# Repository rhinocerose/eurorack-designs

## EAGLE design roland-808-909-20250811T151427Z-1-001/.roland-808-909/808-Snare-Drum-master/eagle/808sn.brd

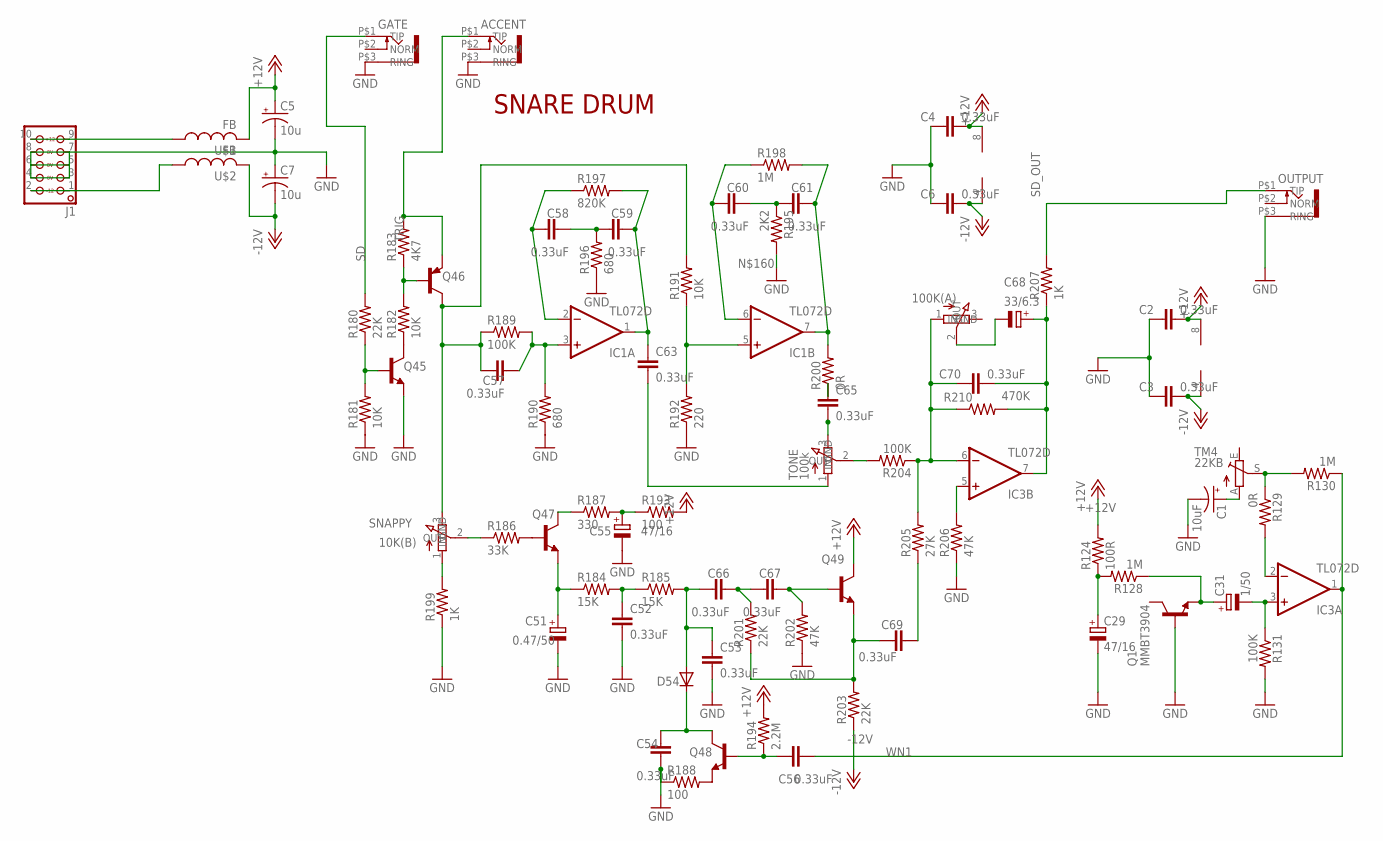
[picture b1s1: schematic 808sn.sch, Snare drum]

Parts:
ACCENT: VERTICALJACKS; KOBICONN_PJM301DM_JACK
C1: 10uF; B45181A
C2, C3, C4, C6, C52, C53, C54, C56, C57, C58, C59, C60, C61, C63, C65, C66, C67, C69, C70: 0.33uF; 0805-CAP
C5, C7: 10u; B45181A
C29: 47/16; E2,5-5
C31: 1/50; E3,5-8
C51: 0.47/50; E3,5-8
C55: 47/16; E2-5
C68: 33/6.3; E2-5
D54: 1N4148SOD-323; SOD323W_INFINEON
GATE: VERTICALJACKS; KOBICONN_PJM301DM_JACK
IC1, IC3: TL072D; SO08
J1: EUROPWR_2X05-OPEN; 2X05_EUROPWR_OPEN
LEVEL: 100K(A); ALPHA_9MM_VERTICAL
OUTPUT: VERTICALJACKS; KOBICONN_PJM301DM_JACK
Q1, Q45, Q47, Q48, Q49: MMBT3904; SOT23-BEC
Q46: MMBT3906; SOT23-BEC
R124: 100R; 0805_RESISTOR
R128, R130, R198: 1M; 0805_RESISTOR
R129, R200: 0R; 0805_RESISTOR
R131, R189, R204: 100K; 0805_RESISTOR
R180, R201, R203: 22K; 0805_RESISTOR
R181, R182, R191: 10K; 0805_RESISTOR
R183: 4K7; 0805_RESISTOR
R184, R185: 15K; 0805_RESISTOR
R186: 33K; 0805_RESISTOR
R187: 330; 0805_RESISTOR
R188, R193: 100; 0805_RESISTOR
R190, R196: 680; 0805_RESISTOR
R192: 220; 0805_RESISTOR
R194: 2.2M; 0805_RESISTOR
R195: 2K2; 0805_RESISTOR
R197: 820K; 0805_RESISTOR
R199, R207: 1K; 0805_RESISTOR
R202, R206: 47K; 0805_RESISTOR
R205: 27K; 0805_RESISTOR
R210: 470K; 0805_RESISTOR
SNAPPY: 10K(B); ALPHA_9MM_VERTICAL
TM4: 22KB; B64Y
TONE: 100k; ALPHA_9MM_VERTICAL
U$1, U$2: FB

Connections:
+12V: C2.2, C4.2, C5.+, IC1.8 (V+), IC3.8 (V+), Q49.C, R124.2, R193.2, R194.2, U$1.P$2 (2)
-12V: C3.2, C6.2, C7.-, IC1.4 (V-), IC3.4 (V-), R203.1, U$2.P$2 (2)
GND: ACCENT.P$3 (RING), C1.-, C2.1, C3.1, C4.1, C5.-, C6.1, C7.+, C29.-, C51.-, C52.2, C53.2, C54.2, C55.-, GATE.P$3 (RING), J1.3, J1.4, J1.5, J1.6, J1.7, J1.8, OUTPUT.P$3 (RING), Q1.B, Q45.E, R131.2, R181.1, R188.1, R190.1, R192.1, R195.2, R196.1, R199.1, R202.1, R206.1
unnamed: IC3.5 (+IN), R206.2
unnamed: C1.+, TM4.A
unnamed: IC3.2 (-IN), R129.2
unnamed: Q45.B, R180.1, R181.2
unnamed: Q46.B, R182.2, R183.1
unnamed: Q45.C, R182.1
unnamed: C57.2, IC1.3 (+IN), R189.2, R190.2
unnamed: C57.1, Q46.C, R189.1, R191.2, SNAPPY.3 (IN)
unnamed: J1.9, J1.10, U$1.P$1 (1)
unnamed: C58.1, IC1.2 (-IN), R197.1
unnamed: C59.2, C63.1, IC1.1 (OUT), R197.2
unnamed: C58.2, C59.1, R196.2
unnamed: C61.2, IC1.7 (OUT), R198.2, R200.2
unnamed: C60.2, C61.1, R195.1
unnamed: IC1.5 (+IN), R191.1, R192.2
unnamed: C63.2, TONE.1 (GND)
unnamed: C65.2, TONE.3 (IN)
unnamed: C65.1, R200.1
unnamed: R199.2, SNAPPY.1 (GND)
unnamed: C52.1, R184.2, R185.1
unnamed: R186.1, SNAPPY.2 (OUT)
unnamed: Q47.B, R186.2
unnamed: Q47.C, R187.1
unnamed: C55.+, R187.2, R193.1
unnamed: C51.+, Q47.E, R184.1
unnamed: C53.1, C66.1, D54.A, R185.2
unnamed: C66.2, C67.1, R201.2
unnamed: C67.2, Q49.B, R202.2
unnamed: C69.1, Q49.E, R201.1, R203.2
unnamed: Q48.E, R188.2
unnamed: C54.1, D54.C, Q48.C
unnamed: C56.1, Q48.B, R194.1
unnamed: R204.2, TONE.2 (OUT)
unnamed: C70.1, IC3.6 (-IN), LEVEL.1 (GND), R204.1, R205.2, R210.1
unnamed: C69.2, R205.1
unnamed: J1.1, J1.2, U$2.P$1 (1)
unnamed: C68.+, C70.2, IC3.7 (OUT), R207.1, R210.2
unnamed: C68.-, LEVEL.2 (OUT)
unnamed: C60.1, IC1.6 (-IN), R198.1
unnamed: C31.-, IC3.3 (+IN), R131.1
unnamed: R129.1, R130.2, TM4.S
unnamed: C31.+, Q1.E, R128.1
unnamed: C29.+, R124.1, R128.2
SD: GATE.P$1 (TIP), R180.2
SD_OUT: OUTPUT.P$1 (TIP), R207.2
TRIG: ACCENT.P$1 (TIP), Q46.E, R183.2
WN1: C56.2, IC3.1 (OUT), R130.1

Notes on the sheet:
SNARE DRUM

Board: 2 copper layers, 80 parts (5 on the bottom side), 50 nets, no tracks yet.

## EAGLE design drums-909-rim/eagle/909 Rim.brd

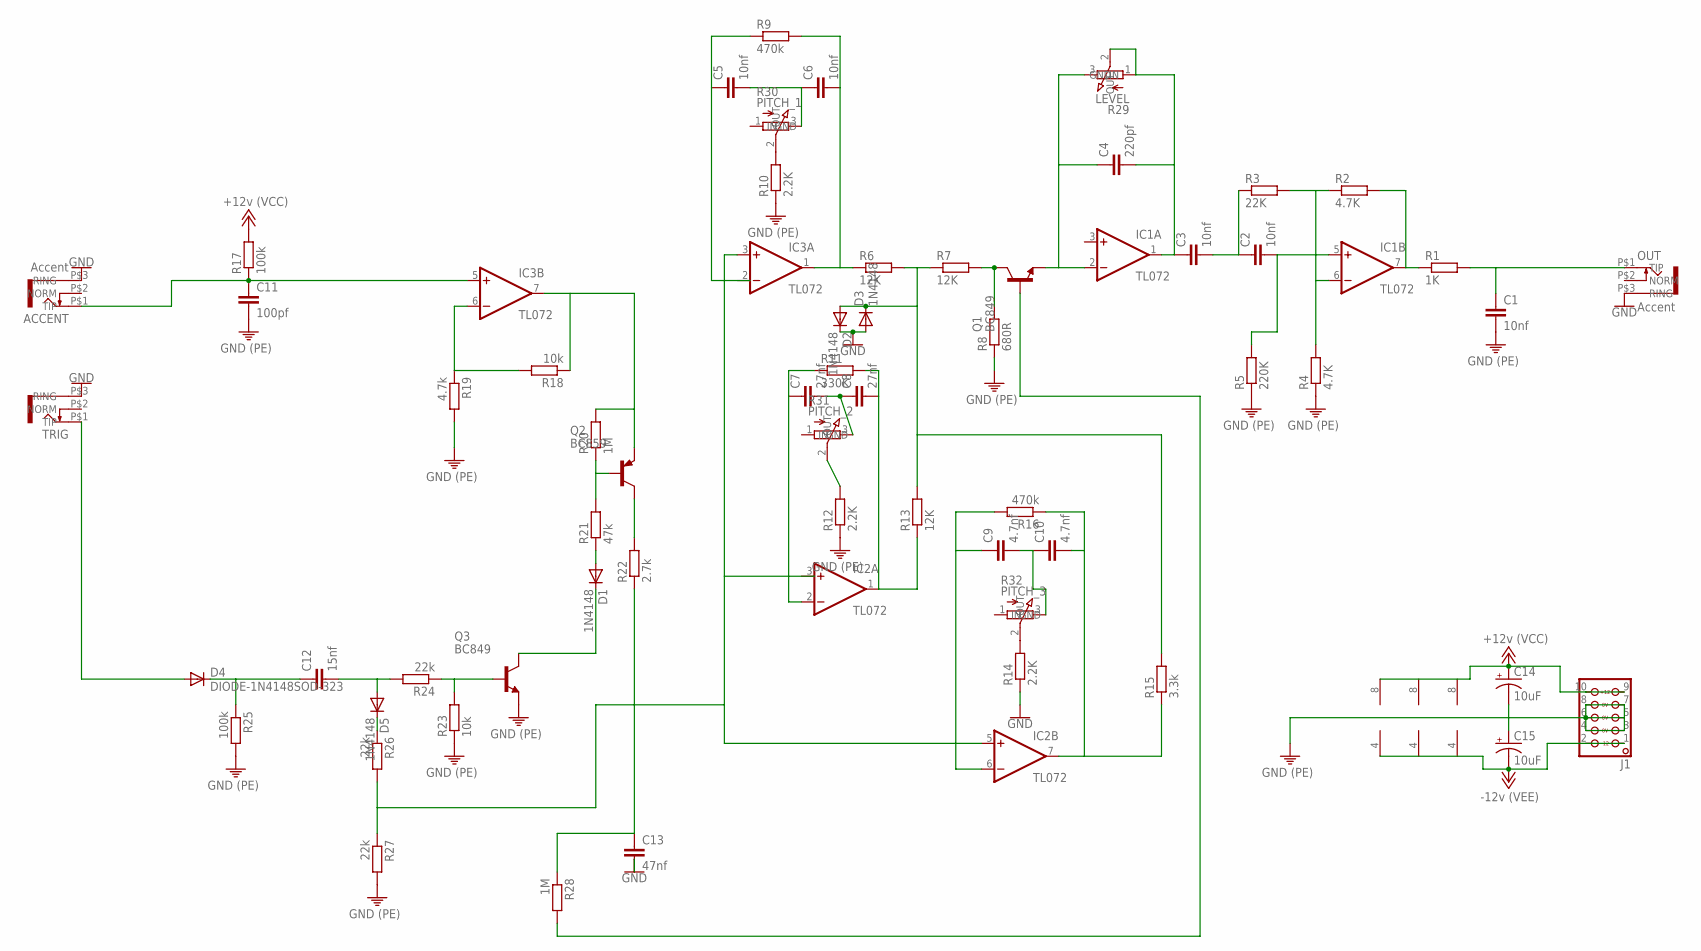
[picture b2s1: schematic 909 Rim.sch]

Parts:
ACCENT: Accent; KOBICONN_PJM301DM_JACK
C1, C2, C3, C5, C6: 10nf; C0603
C4: 220pf; C0603
C7, C8: 27nf; C0603
C9, C10: 4.7nf; C0603
C11: 100pf; C0603
C12: 15nf; C0603
C13: 47nf; C0603
C14, C15: 10uF; E2,5-5
D1, D2, D3, D5: 1N4148; SOD323W_INFINEON
D4: DIODE-1N4148SOD-323; SOD323W_INFINEON
IC1, IC2, IC3: TL072; SO08
J1: HEADER-EUROPWR_2X05-OPEN; 2X05_EUROPWR_OPEN
OUT: Accent; KOBICONN_PJM301DM_JACK
Q1, Q3: BC849; SOT23-BEC
Q2: BC859; SOT23-BEC
R1: 1K; R0603
R2, R4: 4.7K; R0603
R3: 22K; R0603
R5: 220K; R0603
R6, R7, R13: 12K; R0603
R8: 680R; R0603
R9, R16: 470k; R0603
R10, R12, R14: 2.2K; R0603
R11: 330K; R0603
R15: 3.3k; R0603
R17, R25: 100k; R0603
R18, R23: 10k; R0603
R19: 4.7k; R0603
R20, R28: 1M; R0603
R21: 47k; R0603
R22: 2.7k; R0603
R24, R26, R27: 22k; R0603
R29: LEVEL; 9MM_PLS
R30: PITCH_1; 9MM_PLS
R31: PITCH_2; 9MM_PLS
R32: PITCH_3; 9MM_PLS
TRIG: JACK_KOBICONN_PJM301DM_V2; KOBICONN_PJM301DM_JACK

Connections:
+12V: C14.+, IC1.8 (V+), J1.9, J1.10, R17.2
-12V: C15.-, IC1.4 (V-), J1.1, J1.2
GND: ACCENT.P$3 (RING), C1.2, C11.2, C13.2, C14.-, C15.+, D2.C, D3.A, J1.3, J1.4, J1.5, J1.6, J1.7, J1.8, OUT.P$3 (RING), Q3.E, R4.1, R5.1, R8.1, R10.1, R12.1, R14.1, R19.2, R23.1, R25.2, R27.2, TRIG.P$3 (RING)
unnamed: IC1.7 (OUT), R1.1, R2.2
unnamed: C3.1, C4.2, IC1.1 (OUT), R29.1 (GND), R29.2 (OUT)
unnamed: C2.1, C3.2, R3.1
unnamed: C2.2, IC1.5 (+IN), R5.2
unnamed: IC1.6 (-IN), R2.1, R3.2, R4.2
unnamed: C1.1, OUT.P$1 (TIP), R1.2
unnamed: C4.1, IC1.2 (-IN), Q1.E, R29.3 (IN)
unnamed: D2.A, D3.C, R6.2, R7.1, R13.2, R15.2
unnamed: C6.2, IC3.1 (OUT), R6.1, R9.2
unnamed: Q1.C, R7.2, R8.2
unnamed: C5.1, R9.1
unnamed: R10.2, R30.2 (OUT)
unnamed: C7.2, C8.1, R31.3 (IN)
unnamed: C9.2, C10.1, R32.3 (IN)
unnamed: C10.2, IC2.7 (OUT), R15.1, R16.1
unnamed: C5.2, C6.1, R30.3 (IN)
unnamed: C8.2, IC2.1 (OUT), R11.2, R13.1
unnamed: C9.1, IC2.6 (-IN), R16.2
unnamed: Q1.B, R28.2
unnamed: ACCENT.P$1 (TIP), C11.1, IC3.5 (+IN), R17.1
unnamed: IC3.6 (-IN), R18.2, R19.1
unnamed: IC3.7 (OUT), Q2.E, R18.1, R20.2
unnamed: Q2.B, R20.1, R21.2
unnamed: Q2.C, R22.2
unnamed: D1.A, R21.1
unnamed: D5.C, R26.1
unnamed: C12.1, D4.C, R25.1
unnamed: C12.2, D5.A, R24.2
unnamed: IC2.5 (+IN), IC3.3 (+IN), R26.2, R27.1
unnamed: Q3.B, R23.2, R24.1
unnamed: D1.C, Q3.C
unnamed: C13.1, R22.1, R28.1
unnamed: R12.2, R31.2 (OUT)
unnamed: D4.A, TRIG.P$1 (TIP)
unnamed: R14.2, R32.2 (OUT)
unnamed: C7.1, IC2.2 (-IN), R11.1
V+: IC2.8 (V+), IC3.8 (V+)
V-: IC2.4 (V-), IC3.4 (V-)

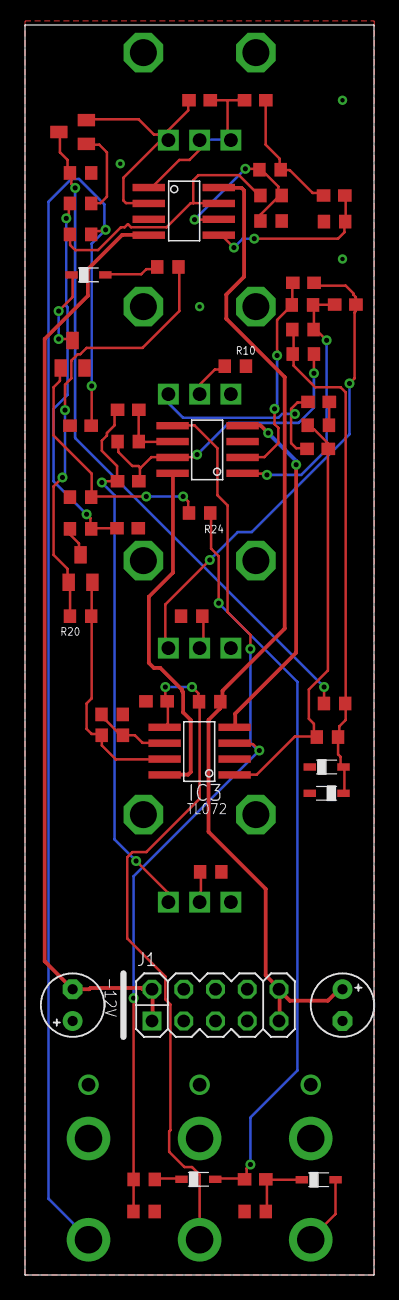
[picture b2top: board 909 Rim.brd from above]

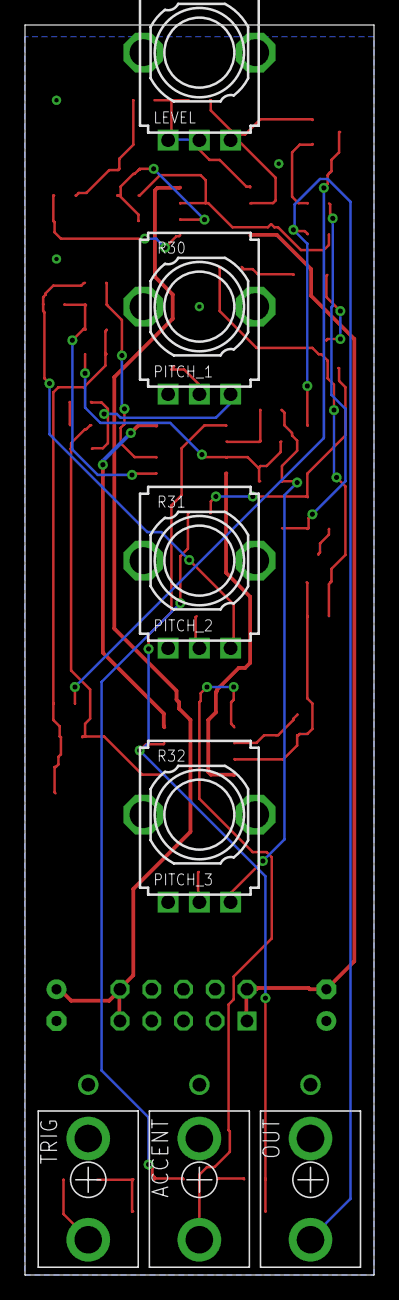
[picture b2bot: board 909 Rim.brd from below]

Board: 2 copper layers, 27.9 x 100.0 mm, 62 parts (7 on the bottom side), 41 nets.

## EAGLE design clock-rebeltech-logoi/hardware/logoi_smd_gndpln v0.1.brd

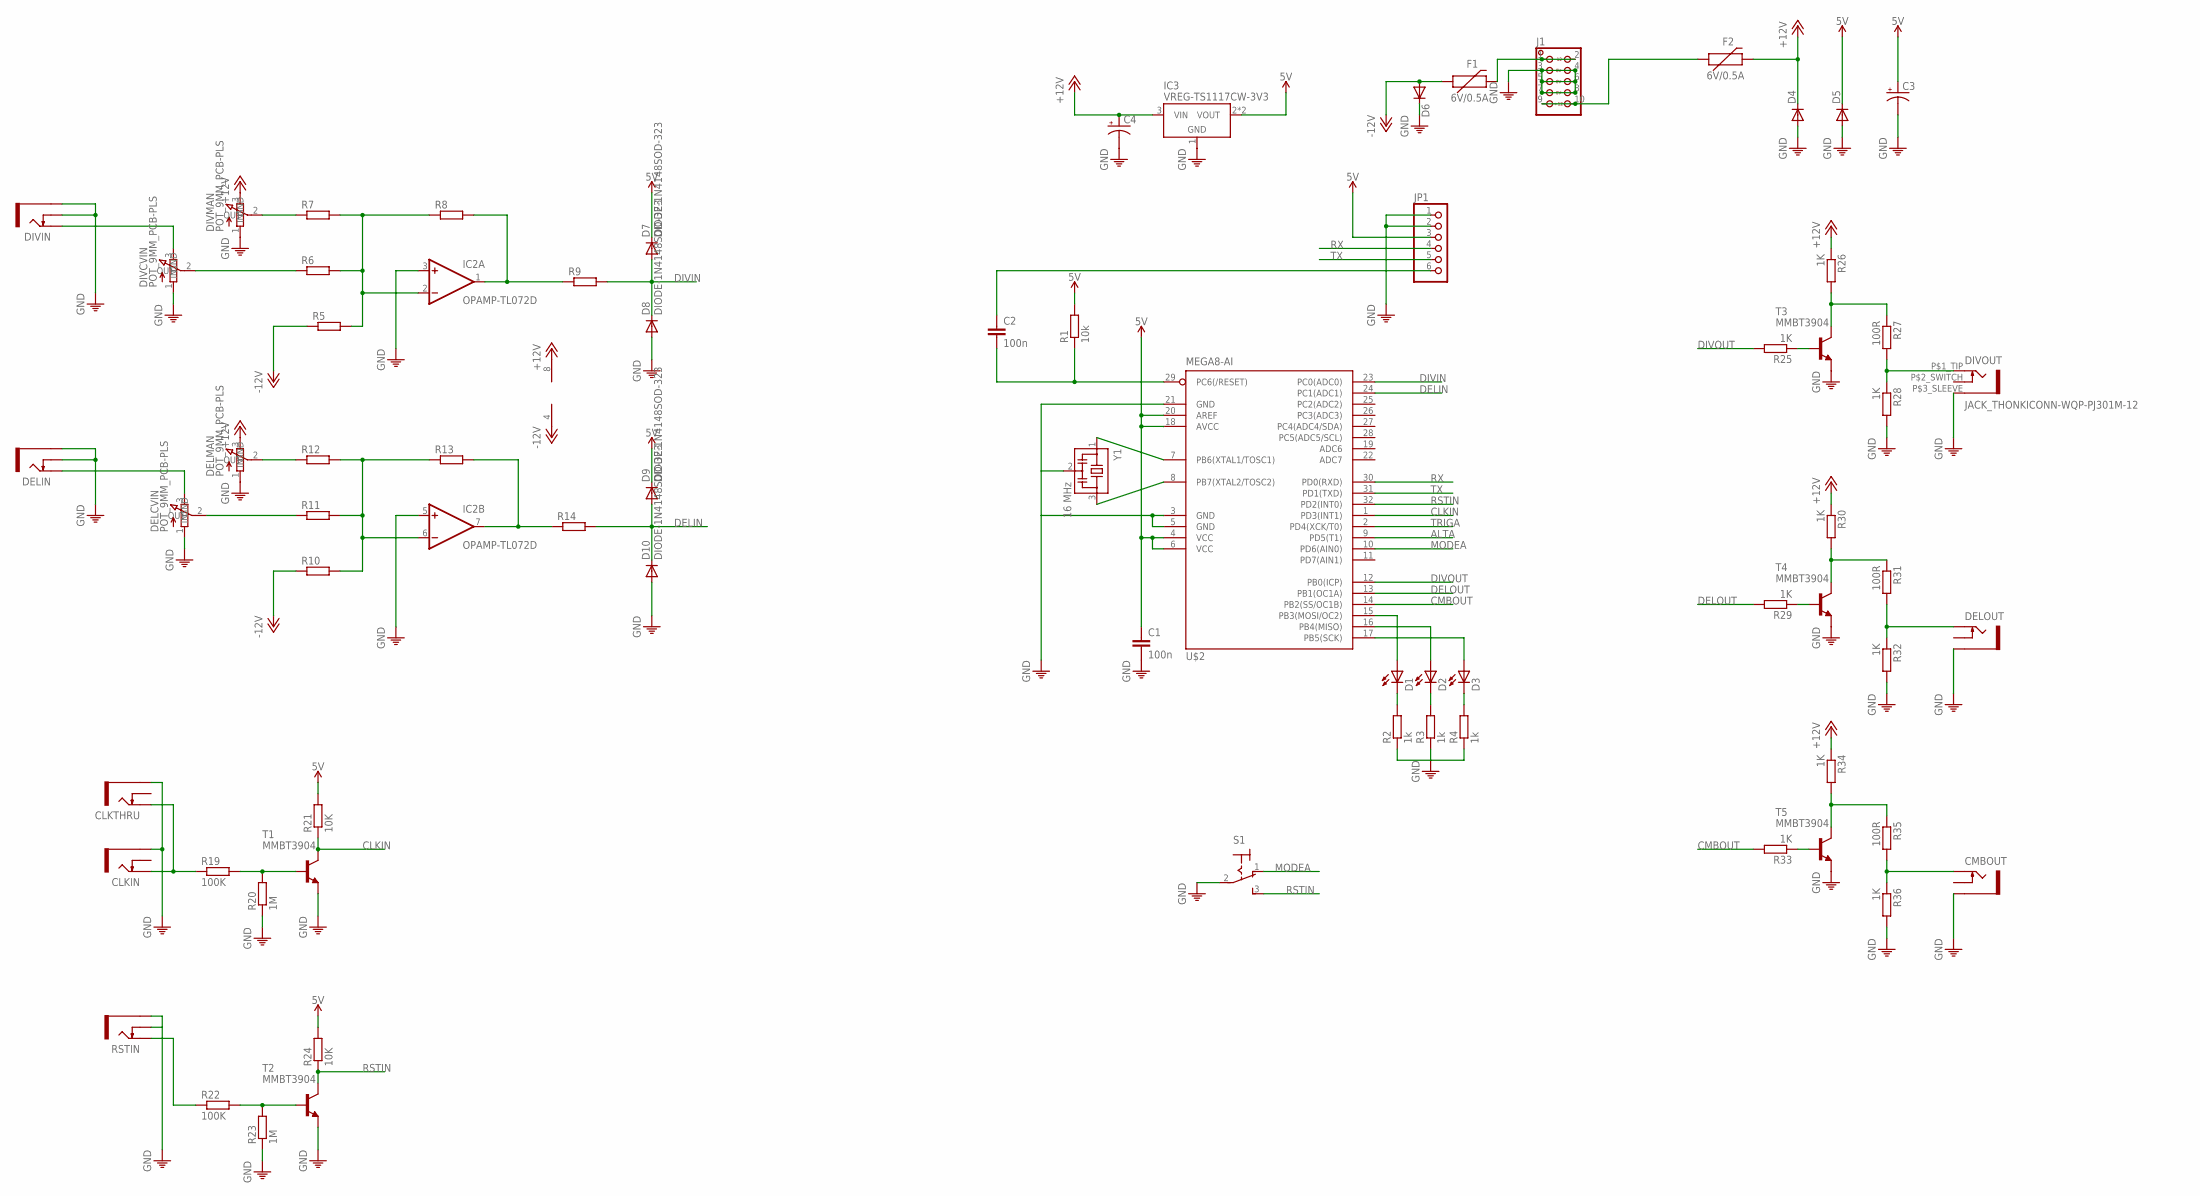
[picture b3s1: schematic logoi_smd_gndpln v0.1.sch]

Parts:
C1, C2: 100n; C0603K
C3, C4: CAPACITOR_POLARIZED-USE2.5-5; E2,5-5
CLKIN: JACK_THONKICONNNEW; WQP-PJ301M-12_JACK
CLKTHRU: JACK_THONKICONNNEW; WQP-PJ301M-12_JACK
CMBOUT: JACK_THONKICONNNEW; WQP-PJ301M-12_JACK
D1, D2, D3: LED3MM
D4, D5, D6: DIODE-DO-214AC; DO-214AC
D7, D8, D9, D10: DIODE-1N4148SOD-323; SOD323W_INFINEON
DELCVIN: POT_9MM_PCB-PLS; 9MM_PLS
DELIN: JACK_THONKICONNNEW; WQP-PJ301M-12_JACK
DELMAN: POT_9MM_PCB-PLS; 9MM_PLS
DELOUT: JACK_THONKICONNNEW; WQP-PJ301M-12_JACK
DIVCVIN: POT_9MM_PCB-PLS; 9MM_PLS
DIVIN: JACK_THONKICONNNEW; WQP-PJ301M-12_JACK
DIVMAN: POT_9MM_PCB-PLS; 9MM_PLS
DIVOUT: JACK_THONKICONN-WQP-PJ301M-12; WQP-PJ301M-12_JACK
F1, F2: 6V/0.5A; 1206
IC2: OPAMP-TL072D; SO08
IC3: VREG-TS1117CW-3V3; SOT223
J1: HEADER-EUROPWR_2X05-OPEN; 2X05_EUROPWR_OPEN
JP1: PINHD-1X6; 1X06
R1: 10k; R0603
R2, R3, R4: 1k; R0603
R5, R6, R7, R8, R9, R10, R11, R12, R13, R14: RESISTOR-EU_R0603; R0603
R19, R22: 100K; R0603
R20, R23: 1M; R0603
R21, R24: 10K; R0603
R25, R26, R28, R29, R30, R32, R33, R34, R36: 1K; R0603
R27, R31, R35: 100R; R0603
RSTIN: JACK_THONKICONNNEW; WQP-PJ301M-12_JACK
S1: SWITCH-SPDT-320-916; 320-916
T1, T2, T3, T4, T5: MMBT3904; SOT23-BEC
U$2: MEGA8-AI; TQFP32-08
Y1: 16 MHz; CSTCR6M

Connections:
5V: C1.1, C3.+, D5.C, D7.C, D9.C, IC3.2 (VOUT), IC3.4 (VOUT), JP1.3, R1.2, R21.2, R24.2, U$2.4 (VCC), U$2.6 (VCC), U$2.18 (AVCC), U$2.20 (AREF)
+12V: C4.+, D4.C, DELMAN.3 (IN), DIVMAN.3 (IN), F2.2, IC2.8 (V+), IC3.3 (VIN), R26.1, R30.1, R34.1
-12V: D6.A, F1.1, IC2.4 (V-), R5.1, R10.1
ALTA: U$2.9 (PD5(T1))
CLKIN: R21.1, T1.C, U$2.1 (PD3(INT1))
CMBOUT: R33.2, U$2.14 (PB2(SS/OC1B))
DELIN: D9.A, D10.C, R14.2, U$2.24 (PC1(ADC1))
DELOUT: R29.2, U$2.13 (PB1(OC1A))
DIVIN: D7.A, D8.C, R9.2, U$2.23 (PC0(ADC0))
DIVOUT: R25.2, U$2.12 (PB0(ICP))
MODEA: S1.1 (O), U$2.10 (PD6(AIN0))
unnamed: U$2.7 (PB6(XTAL1/TOSC1)), Y1.1
unnamed: U$2.8 (PB7(XTAL2/TOSC2)), Y1.3
unnamed: F1.2, J1.1, J1.2
unnamed: C2.2, R1.1, U$2.29 (PC6(/RESET))
unnamed: C2.1, JP1.6
unnamed: F2.1, J1.9, J1.10
unnamed: IC2.2 (-IN), R5.2, R6.2, R7.2, R8.1
unnamed: IC2.1 (OUT), R8.2, R9.1
unnamed: R25.1, T3.B
unnamed: IC2.6 (-IN), R10.2, R11.2, R12.2, R13.1
unnamed: R26.2, R27.1, T3.C
unnamed: IC2.7 (OUT), R13.2, R14.1
unnamed: DIVOUT.P$1_TIP (2), R27.2, R28.1
unnamed: DIVCVIN.3 (IN), DIVIN.P$1_TIP (TIP)
unnamed: DIVCVIN.2 (OUT), R6.1
unnamed: DIVMAN.2 (OUT), R7.1
unnamed: D1.K (C), R2.2
unnamed: D2.K (C), R3.2
unnamed: D3.K (C), R4.2
unnamed: D1.A, U$2.15 (PB3(MOSI/OC2))
unnamed: D2.A, U$2.16 (PB4(MISO))
unnamed: D3.A, U$2.17 (PB5(SCK))
unnamed: DELCVIN.2 (OUT), R11.1
unnamed: DELCVIN.3 (IN), DELIN.P$1_TIP (TIP)
unnamed: DELMAN.2 (OUT), R12.1
unnamed: CLKIN.P$1_TIP (TIP), CLKTHRU.P$1_TIP (TIP), R19.1
unnamed: R19.2, R20.2, T1.B
unnamed: R22.1, RSTIN.P$1_TIP (TIP)
unnamed: R22.2, R23.2, T2.B
unnamed: R29.1, T4.B
unnamed: R30.2, R31.1, T4.C
unnamed: DELOUT.P$1_TIP (TIP), R31.2, R32.1
unnamed: R33.1, T5.B
unnamed: R34.2, R35.1, T5.C
unnamed: CMBOUT.P$1_TIP (TIP), R35.2, R36.1
PE: C1.2, C3.-, C4.-, CLKIN.P$3_SLEEVE (SLEEVE), CLKTHRU.P$3_SLEEVE (SLEEVE), CMBOUT.P$3_SLEEVE (SLEEVE), D4.A, D5.A, D6.C, D8.A, D10.A, DELCVIN.1 (GND), DELIN.P$2_SWITCH (SWITCH), DELIN.P$3_SLEEVE (SLEEVE), DELMAN.1 (GND), DELOUT.P$3_SLEEVE (SLEEVE), DIVCVIN.1 (GND), DIVIN.P$2_SWITCH (SWITCH), DIVIN.P$3_SLEEVE (SLEEVE), DIVMAN.1 (GND), DIVOUT.P$3_SLEEVE (1), IC2.3 (+IN), IC2.5 (+IN), IC3.1 (GND), J1.3, J1.4, J1.5, J1.6, J1.7, J1.8, JP1.1, JP1.2, R2.1, R3.1, R4.1, R20.1, R23.1, R28.2, R32.2, R36.2, RSTIN.P$2_SWITCH (SWITCH), RSTIN.P$3_SLEEVE (SLEEVE), S1.2, T1.E, T2.E, T3.E, T4.E, T5.E, U$2.3 (GND), U$2.5 (GND), U$2.21 (GND), Y1.2
RSTIN: R24.1, S1.3 (S), T2.C, U$2.32 (PD2(INT0))
RX: JP1.4, U$2.30 (PD0(RXD))
TRIGA: U$2.2 (PD4(XCK/T0))
TX: JP1.5, U$2.31 (PD1(TXD))

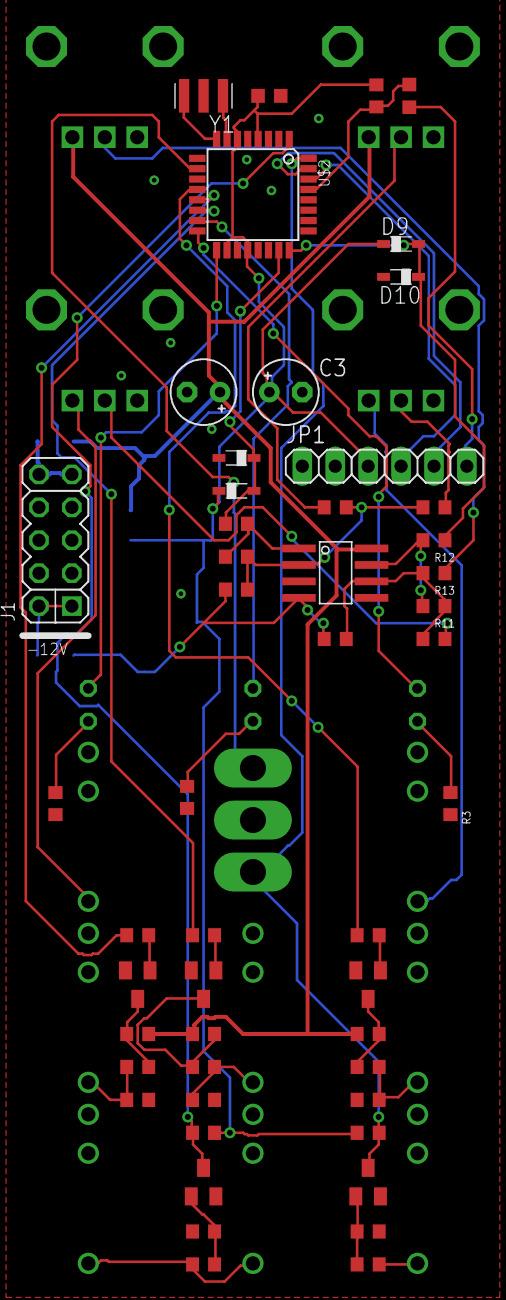
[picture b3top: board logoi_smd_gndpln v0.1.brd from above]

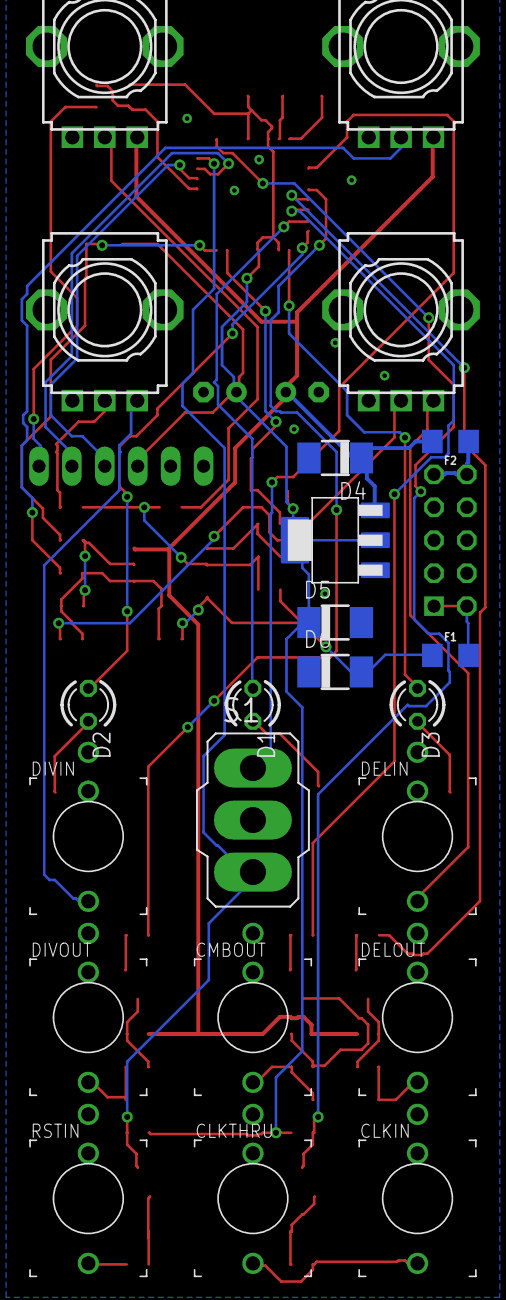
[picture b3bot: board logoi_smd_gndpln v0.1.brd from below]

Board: 2 copper layers, 72 parts (22 on the bottom side), 49 nets.

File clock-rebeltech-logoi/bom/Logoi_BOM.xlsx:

R19 | 100K | RESISTOR-EU_R0603 | R0603
R22 | 100K | RESISTOR-EU_R0603 | R0603
C1 | 100n | CAPACITOR-EUC0603K | C0603K
C2 | 100n | CAPACITOR-EUC0603K | C0603K
C6 | 100n | CAPACITOR-EUC0603K | C0603K
C7 | 100n | CAPACITOR-EUC0603K | C0603K
R27 | 100R | RESISTOR-EU_R0603 | R0603
R31 | 100R | RESISTOR-EU_R0603 | R0603
R35 | 100R | RESISTOR-EU_R0603 | R0603
R1 | 10k | RESISTOR-EU_R0603 | R0603
R21 | 10K | RESISTOR-EU_R0603 | R0603
R24 | 10K | RESISTOR-EU_R0603 | R0603
C4 | 10u | CAPACITOR_POLARIZED-USB | PANASONIC_B
C5 | 10u | CAPACITOR_POLARIZED-USB | PANASONIC_B
R5 | 120k | RESISTOR-EU_R0603 | R0603
R7 | 120k | RESISTOR-EU_R0603 | R0603
R10 | 120k | RESISTOR-EU_R0603 | R0603
R12 | 120k | RESISTOR-EU_R0603 | R0603
Y1 | 16 MHz | CSTCR6M00G53Z | CSTCR6M
R2 | 1k | RESISTOR-EU_R0603 | R0603
R3 | 1k | RESISTOR-EU_R0603 | R0603
R4 | 1k | RESISTOR-EU_R0603 | R0603
R25 | 1K | RESISTOR-EU_R0603 | R0603
R26 | 1K | RESISTOR-EU_R0603 | R0603
R28 | 1K | RESISTOR-EU_R0603 | R0603
R29 | 1K | RESISTOR-EU_R0603 | R0603
R30 | 1K | RESISTOR-EU_R0603 | R0603
R32 | 1K | RESISTOR-EU_R0603 | R0603
R33 | 1K | RESISTOR-EU_R0603 | R0603
R34 | 1K | RESISTOR-EU_R0603 | R0603
R36 | 1K | RESISTOR-EU_R0603 | R0603
R20 | 1M | RESISTOR-EU_R0603 | R0603
R23 | 1M | RESISTOR-EU_R0603 | R0603
R6 | 51k | RESISTOR-EU_R0603 | R0603
R8 | 51k | RESISTOR-EU_R0603 | R0603
R9 | 51k | RESISTOR-EU_R0603 | R0603
R11 | 51k | RESISTOR-EU_R0603 | R0603
R13 | 51k | RESISTOR-EU_R0603 | R0603
R14 | 51k | RESISTOR-EU_R0603 | R0603
F1 | 6V/0.5A | FUSE-PPTC_HALF-AMP | L1206
F2 | 6V/0.5A | FUSE-PPTC_HALF-AMP | L1206
IC1 | 7805DT | 7805DT | TO252
U$2 | ATMEGA328 | MEGA8-AI | TQFP32-08
D7 | DIODE-1N4148SOD-323 | DIODE-1N4148SOD-323 | SOD323W_INFINEON | ****DNP*****
D8 | DIODE-1N4148SOD-323 | DIODE-1N4148SOD-323 | SOD323W_INFINEON | ****DNP*****
D9 | DIODE-1N4148SOD-323 | DIODE-1N4148SOD-323 | SOD323W_INFINEON | ****DNP*****
D10 | DIODE-1N4148SOD-323 | DIODE-1N4148SOD-323 | SOD323W_INFINEON | ****DNP*****
J1 | HEADER-EUROPWR_2X05-OPE | HEADER-EUROPWR_2X05-OPEN | 2X05_EUROPWR_OPEN
CLKIN | JACK_THONKICONNNEW | JACK_THONKICONNNEW | WQP-PJ301M-12_JACK
CLKTHRU | JACK_THONKICONNNEW | JACK_THONKICONNNEW | WQP-PJ301M-12_JACK
CMBOUT | JACK_THONKICONNNEW | JACK_THONKICONNNEW | WQP-PJ301M-12_JACK
DELIN | JACK_THONKICONNNEW | JACK_THONKICONNNEW | WQP-PJ301M-12_JACK
DELOUT | JACK_THONKICONNNEW | JACK_THONKICONNNEW | WQP-PJ301M-12_JACK
DIVIN | JACK_THONKICONNNEW | JACK_THONKICONNNEW | WQP-PJ301M-12_JACK
DIVOUT | JACK_THONKICONNNEW | JACK_THONKICONNNEW | WQP-PJ301M-12_JACK
RSTIN | JACK_THONKICONNNEW | JACK_THONKICONNNEW | WQP-PJ301M-12_JACK
T1 | MMBT3904 | TRANSISTOR-NPN-MMBT3904LT1SO | T23-BEC SOT23-BEC
T2 | MMBT3904 | TRANSISTOR-NPN-MMBT3904LT1SO | T23-BEC SOT23-BEC
T3 | MMBT3904 | TRANSISTOR-NPN-MMBT3904LT1SO | T23-BEC SOT23-BEC
T4 | MMBT3904 | TRANSISTOR-NPN-MMBT3904LT1SO | T23-BEC SOT23-BEC
T5 | MMBT3904 | TRANSISTOR-NPN-MMBT3904LT1SO | T23-BEC SOT23-BEC
IC2 | OPAMP-TL072D | OPAMP-TL072D | SO08
DELCVIN | POT_9MM_PCB-PLS | POT_9MM_PCB-PLS | 9MM_PLS
DELMAN | POT_9MM_PCB-PLS | POT_9MM_PCB-PLS | 9MM_PLS
DIVCVIN | POT_9MM_PCB-PLS | POT_9MM_PCB-PLS | 9MM_PLS
DIVMAN | POT_9MM_PCB-PLS | POT_9MM_PCB-PLS | 9MM_PLS
D4 | SS12 | DIODE-DO-214AC | DO-214AC
D6 | SS12 | DIODE-DO-214AC | DO-214AC
Part | Value | Device | Package
D1 |  | LED3MM | LED3MM
D2 |  | LED3MM | LED3MM
D3 |  | LED3MM | LED3MM
JP1 |  | PINHD-1X6 | 1X06
S1 |  | SWITCH-SPDT-320-916 | 320-916

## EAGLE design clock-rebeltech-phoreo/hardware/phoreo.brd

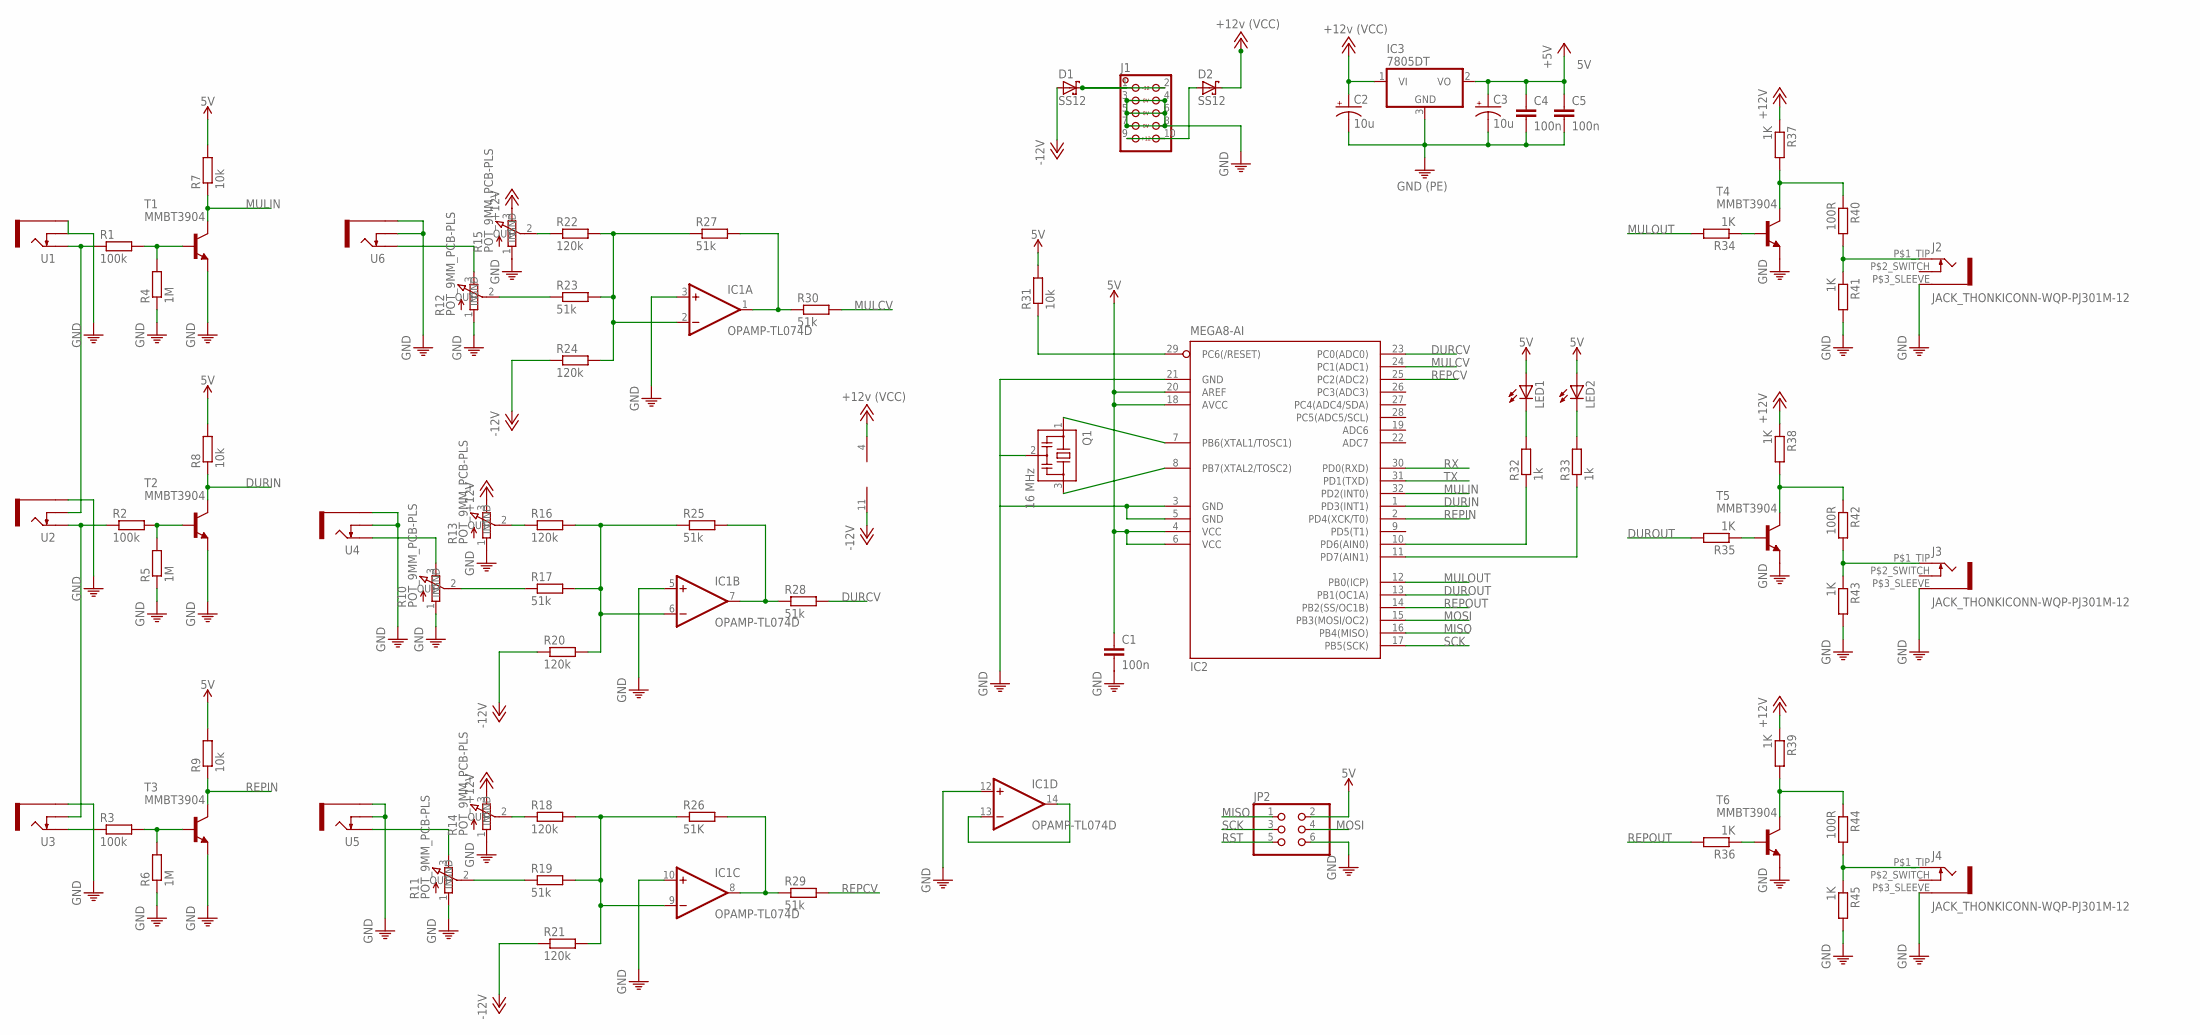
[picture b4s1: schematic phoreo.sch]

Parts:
C1: 100n; C0603K
C2, C3: 10u; PANASONIC_B
C4, C5: 100n; C0603
D1, D2: SS12; SMA_DO214AC
IC1: OPAMP-TL074D; SO14
IC2: MEGA8-AI; TQFP32-08
IC3: 7805DT; TO252
J1: HEADER-EUROPWR_2X05-OPEN; 2X05_EUROPWR_OPEN
J2, J3, J4: JACK_THONKICONN-WQP-PJ301M-12; WQP-PJ301M-12_JACK
JP2: PINHD-2X3; 2X03
LED1, LED2: LED3MM
Q1: 16 MHz; CSTCR6M
R1, R2, R3: 100k; R0603
R4, R5, R6: 1M; R0603
R7, R8, R9, R31: 10k; R0603
R10, R11, R12, R13, R14, R15: POT_9MM_PCB-PLS; 9MM_PLS
R16, R18, R20, R21, R22, R24: 120k; R0603
R17, R19, R23, R25, R27, R28, R29, R30: 51k; R0603
R26: 51K; R0603
R32, R33: 1k; R0603
R34, R35, R36, R37, R38, R39, R41, R43, R45: 1K; R0603
R40, R42, R44: 100R; R0603
T1, T2, T3, T4, T5, T6: MMBT3904; SOT23-BEC
U1, U2, U3, U4, U5, U6: mulcv; WQP-PJ301M-12_JACK

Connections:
5V: C1.1, C3.+, C4.1, C5.1, IC2.4 (VCC), IC2.6 (VCC), IC2.18 (AVCC), IC2.20 (AREF), IC3.2 (VO), JP2.2, LED1.A, LED2.A, R7.2, R8.2, R9.2, R31.2
+12V: C2.+, D2.C, IC1.4 (V+), IC3.1 (VI), R13.3 (IN), R14.3 (IN), R15.3 (IN), R37.1, R38.1, R39.1
-12V: D1.A, IC1.11 (V-), R20.1, R21.1, R24.1
DURCV: IC2.23 (PC0(ADC0)), R28.2
DURIN: IC2.1 (PD3(INT1)), R8.1, T2.C
DUROUT: IC2.13 (PB1(OC1A)), R35.2
MISO: IC2.16 (PB4(MISO)), JP2.1
MOSI: IC2.15 (PB3(MOSI/OC2)), JP2.4
MULCV: IC2.24 (PC1(ADC1)), R30.2
MULIN: IC2.32 (PD2(INT0)), R7.1, T1.C
MULOUT: IC2.12 (PB0(ICP)), R34.2
unnamed: IC2.7 (PB6(XTAL1/TOSC1)), Q1.1
unnamed: D1.C, J1.1, J1.2
unnamed: IC2.8 (PB7(XTAL2/TOSC2)), Q1.3
unnamed: IC2.29 (PC6(/RESET)), R31.1
unnamed: R34.1, T4.B
unnamed: D2.A, J1.9, J1.10
unnamed: IC2.10 (PD6(AIN0)), R32.1
unnamed: IC2.11 (PD7(AIN1)), R33.1
unnamed: LED1.K (C), R32.2
unnamed: LED2.K (C), R33.2
unnamed: IC1.2 (-IN), R22.2, R23.2, R24.2, R27.1
unnamed: IC1.1 (OUT), R27.2, R30.1
unnamed: IC1.6 (-IN), R16.2, R17.2, R20.2, R25.1
unnamed: IC1.7 (OUT), R25.2, R28.1
unnamed: R10.3 (IN), U4.P$1_TIP (TIP)
unnamed: R10.2 (OUT), R17.1
unnamed: R12.3 (IN), U6.P$1_TIP (TIP)
unnamed: R12.2 (OUT), R23.1
unnamed: R15.2 (OUT), R22.1
unnamed: R13.2 (OUT), R16.1
unnamed: IC1.9 (-IN), R18.2, R19.2, R21.2, R26.1
unnamed: IC1.8 (OUT), R26.2, R29.1
unnamed: R11.3 (IN), U5.P$1_TIP (TIP)
unnamed: R11.2 (OUT), R19.1
unnamed: R14.2 (OUT), R18.1
unnamed: IC1.13 (-IN), IC1.14 (OUT)
unnamed: R37.2, R40.1, T4.C
unnamed: J2.P$1_TIP (2), R40.2, R41.1
unnamed: R35.1, T5.B
unnamed: R38.2, R42.1, T5.C
unnamed: J3.P$1_TIP (2), R42.2, R43.1
unnamed: R36.1, T6.B
unnamed: R39.2, R44.1, T6.C
unnamed: J4.P$1_TIP (2), R44.2, R45.1
unnamed: R1.1, U1.P$1_TIP (TIP), U2.P$2_SWITCH (SWITCH)
unnamed: R1.2, R4.2, T1.B
unnamed: R2.1, U2.P$1_TIP (TIP), U3.P$2_SWITCH (SWITCH)
unnamed: R2.2, R5.2, T2.B
unnamed: R3.1, U3.P$1_TIP (TIP)
unnamed: R3.2, R6.2, T3.B
PE: C1.2, C2.-, C3.-, C4.2, C5.2, IC1.3 (+IN), IC1.5 (+IN), IC1.10 (+IN), IC1.12 (+IN), IC2.3 (GND), IC2.5 (GND), IC2.21 (GND), IC3.3 (GND), J1.3, J1.4, J1.5, J1.6, J1.7, J1.8, J2.P$3_SLEEVE (1), J3.P$3_SLEEVE (1), J4.P$3_SLEEVE (1), JP2.6, Q1.2, R4.1, R5.1, R6.1, R10.1 (GND), R11.1 (GND), R12.1 (GND), R13.1 (GND), R14.1 (GND), R15.1 (GND), R41.2, R43.2, R45.2, T1.E, T2.E, T3.E, T4.E, T5.E, T6.E, U1.P$2_SWITCH (SWITCH), U1.P$3_SLEEVE (SLEEVE), U2.P$3_SLEEVE (SLEEVE), U3.P$3_SLEEVE (SLEEVE), U4.P$2_SWITCH (SWITCH), U4.P$3_SLEEVE (SLEEVE), U5.P$2_SWITCH (SWITCH), U5.P$3_SLEEVE (SLEEVE), U6.P$2_SWITCH (SWITCH), U6.P$3_SLEEVE (SLEEVE)
REPCV: IC2.25 (PC2(ADC2)), R29.2
REPIN: IC2.2 (PD4(XCK/T0)), R9.1, T3.C
REPOUT: IC2.14 (PB2(SS/OC1B)), R36.2
RST: JP2.5
RX: IC2.30 (PD0(RXD))
SCK: IC2.17 (PB5(SCK)), JP2.3
TX: IC2.31 (PD1(TXD))

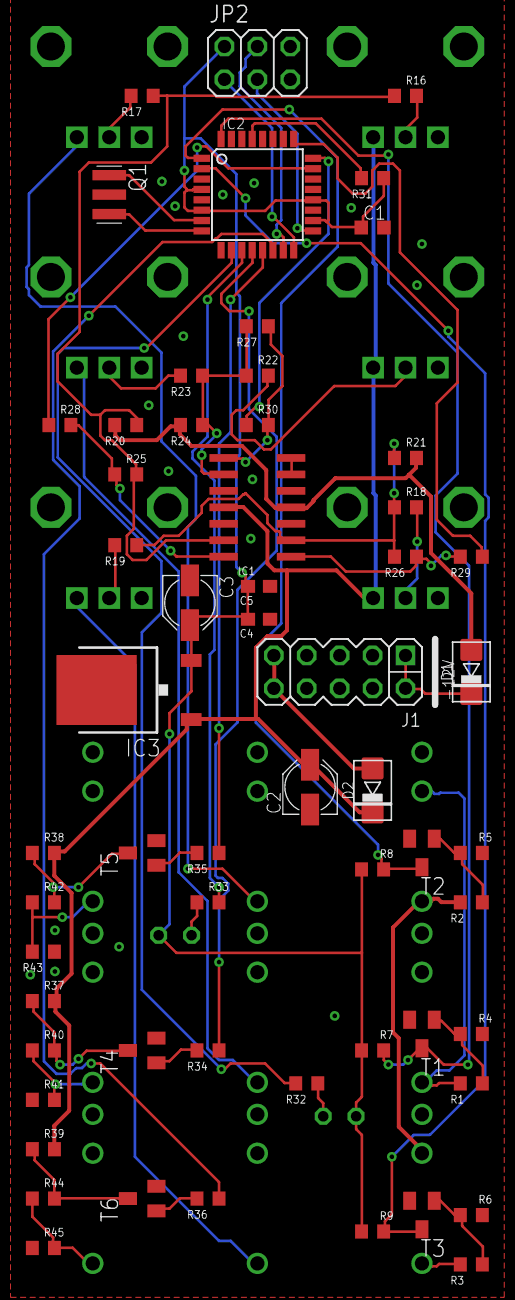
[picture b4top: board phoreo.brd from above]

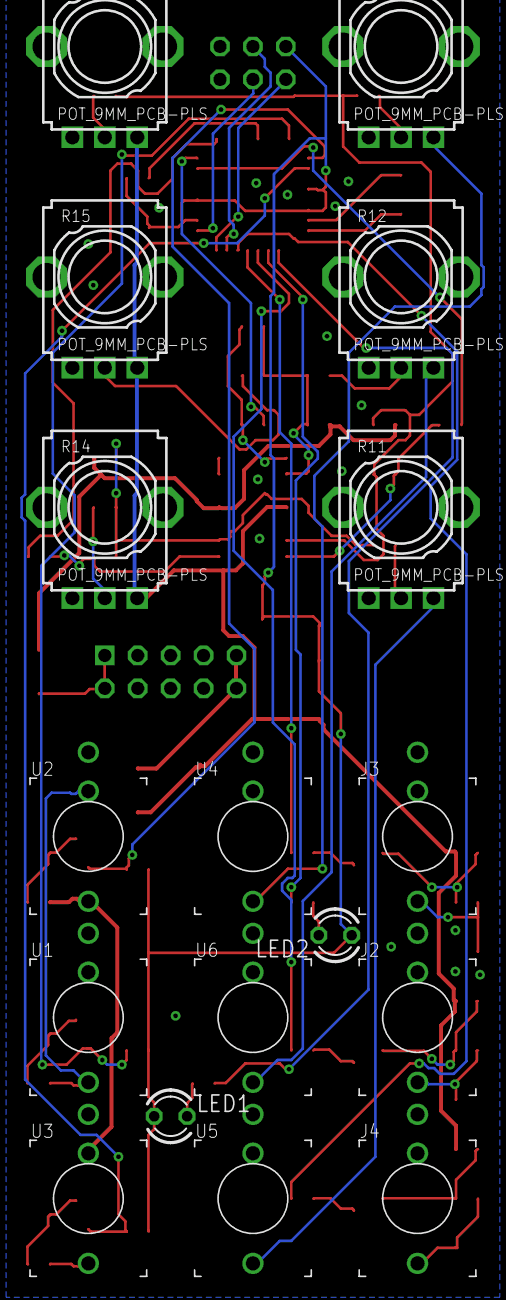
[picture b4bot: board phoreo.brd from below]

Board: 2 copper layers, 75 parts (17 on the bottom side), 56 nets.

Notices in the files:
parts and their libraries:
SparkFun-PowerSymbols: Licensing: Creative Commons ShareAlike 4.0 International - https://creativecommons.org/licenses/by-sa/4.0
